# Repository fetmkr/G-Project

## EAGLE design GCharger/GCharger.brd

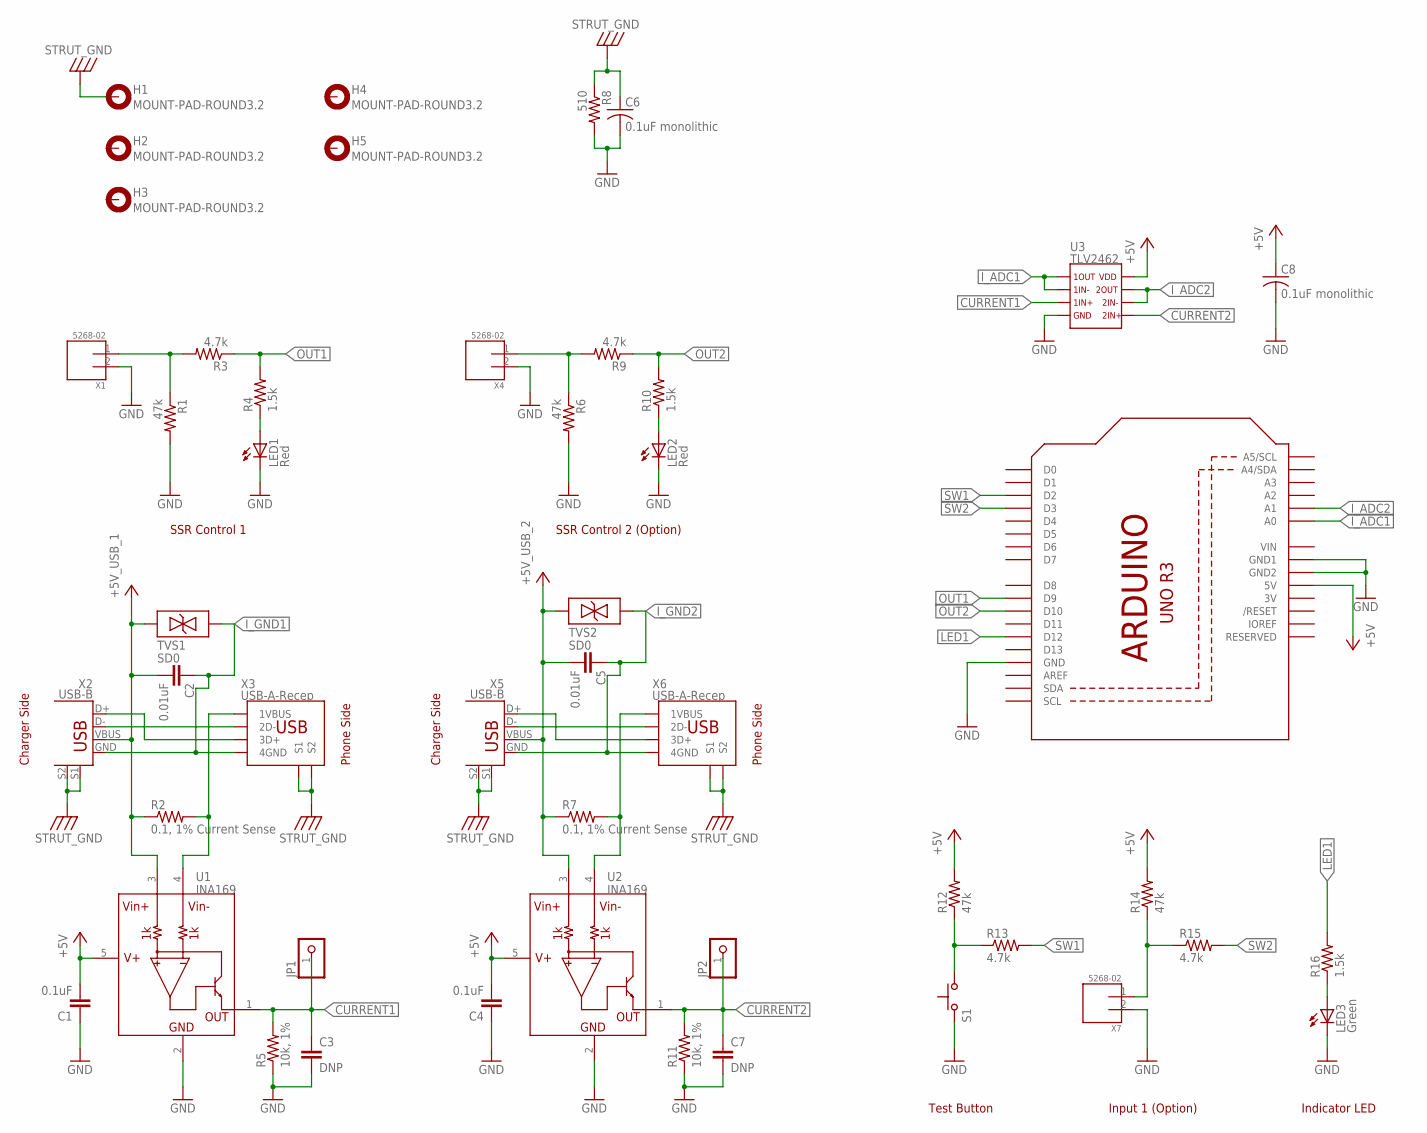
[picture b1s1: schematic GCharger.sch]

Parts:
C1, C4: 0.1uF; C0603(1608)
C2, C5: 0.01uF; C0603(1608)
C3, C7: DNP; C0603(1608)
C6, C8: 0.1uF monolithic; C050-024X044
H1, H2, H3, H4, H5: MOUNT-PAD-ROUND3.2; 3.2-PAD-ROUND
JP1, JP2: PINHD-1X1CB; 1X01-CLEANBIG
LED1, LED2: Red; LED3MM
LED3: Green; LED3MM
R1, R6, R12, R14: 47k; 0805-THM
R2, R7: 0.1, 1% Current Sense; 1206
R3, R9, R13, R15: 4.7k; 0805-THM
R4, R10, R16: 1.5k; 0805-THM
R5, R11: 10k, 1%; 0805-THM
R8: 510; 0805-THM
S1: SWITCH; SKHLACA010
TVS1, TVS2: SD0; SOD-323
U1, U2: INA169; SOT23-5
U3: TLV2462; SO8
U4: ARDUINOR3-TPLACE; ARDUINOR3
X1, X4, X7: 5268-02; 5628-02
X2, X5: USB-B; USB-B-PTH
X3, X6: USB-A-Recep; USB-A-RECEPT

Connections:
3V: U4.3V
+5V: C1.2, C4.2, C8.1, R12.2, R14.2, U1.5 (V+), U2.5 (V+), U3.8, U4.5V
+5V_USB_1: C2.2, R2.1, TVS1.1, U1.3 (VIN+), X2.VBUS
+5V_USB_2: C5.2, R7.1, TVS2.1, U2.3 (VIN+), X5.VBUS
CURRENT1: C3.1, JP1.1, R5.2, U1.1 (OUT), U3.3
CURRENT2: C7.1, JP2.1, R11.2, U2.1 (OUT), U3.5
GND: C1.1, C3.2, C4.1, C6.2, C7.2, C8.2, LED1.K (C), LED2.K (C), LED3.K (C), R1.2, R5.1, R6.2, R8.2, R11.1, S1.P$1, U1.2 (GND), U2.2 (GND), U3.4, U4.GND, U4.GND1, U4.GND2, X1.2, X4.2, X7.2
I_ADC1: U3.1, U3.2, U4.A0
I_ADC2: U3.6, U3.7, U4.A1
I_GND1: C2.1, TVS1.2, X2.GND, X3.4 (4GND)
I_GND2: C5.1, TVS2.2, X5.GND, X6.4 (4GND)
LED1: R16.2, U4.D12
unnamed: X5.D-, X6.2 (2D-)
unnamed: X5.D+, X6.3 (3D+)
unnamed: R1.1, R3.2, X1.1
unnamed: X2.D-, X3.2 (2D-)
unnamed: X2.D+, X3.3 (3D+)
unnamed: R7.2, U2.4 (VIN-), X6.1 (1VBUS)
unnamed: R12.1, R13.1, S1.P$2
unnamed: R6.1, R9.2, X4.1
unnamed: R2.2, U1.4 (VIN-), X3.1 (1VBUS)
unnamed: LED2.A, R10.1
unnamed: LED1.A, R4.1
unnamed: LED3.A, R16.1
unnamed: R14.1, R15.1, X7.1
OUT1: R3.1, R4.2, U4.D9
OUT2: R9.1, R10.2, U4.D10
STRUT_GND: C6.1, H1.B3,2, R8.1, X2.S1, X2.S2, X3.S1, X3.S2, X5.S1, X5.S2, X6.S1, X6.S2
SW1: R13.2, U4.D2
SW2: R15.2, U4.D3
VIN: U4.VIN

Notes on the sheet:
SSR Control 1
SSR Control 2 (Option)
Charger Side
Phone Side
Test Button
Input 1 (Option)
Indicator LED

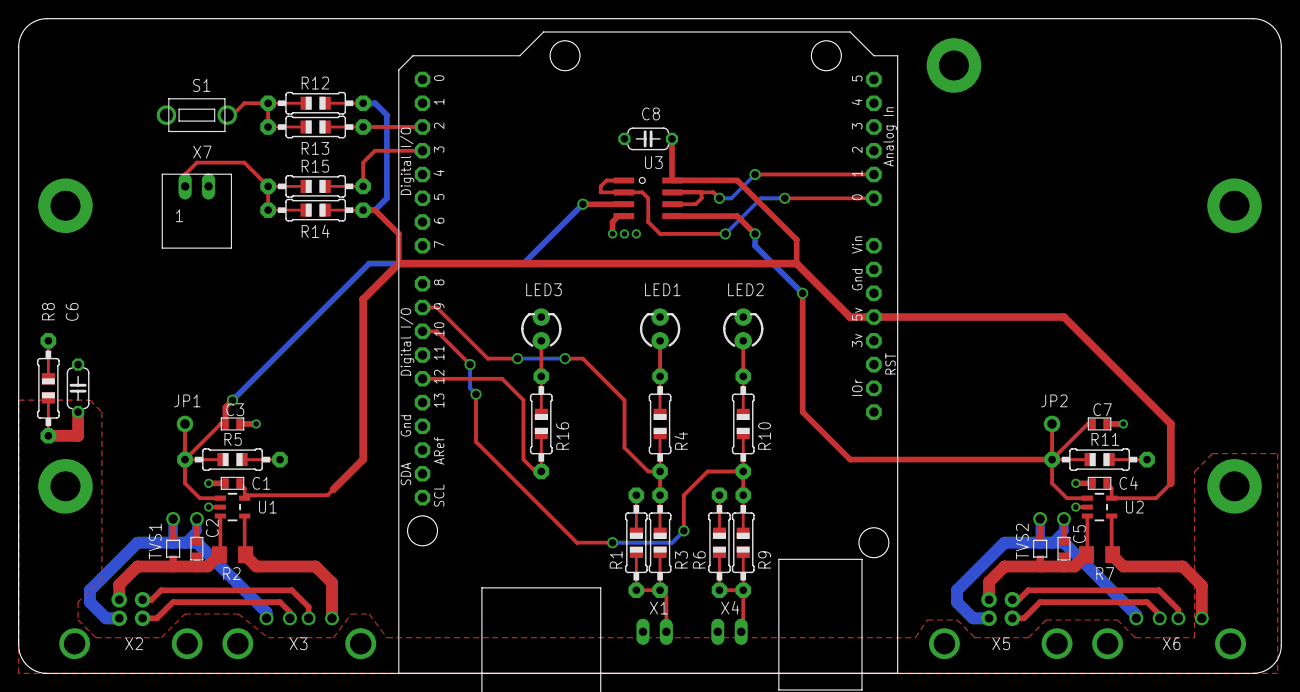
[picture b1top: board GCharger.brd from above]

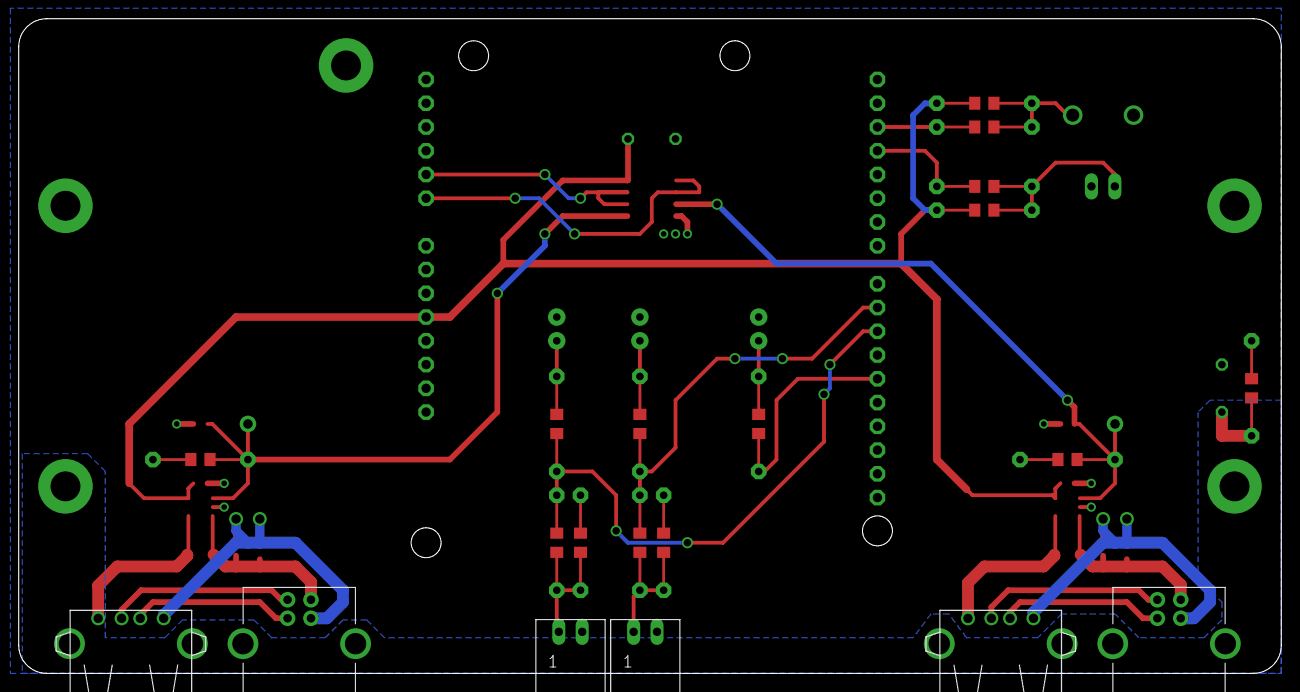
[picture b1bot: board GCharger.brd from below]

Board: 2 copper layers, 135.0 x 70.0 mm, 48 parts (6 on the bottom side), 29 nets.

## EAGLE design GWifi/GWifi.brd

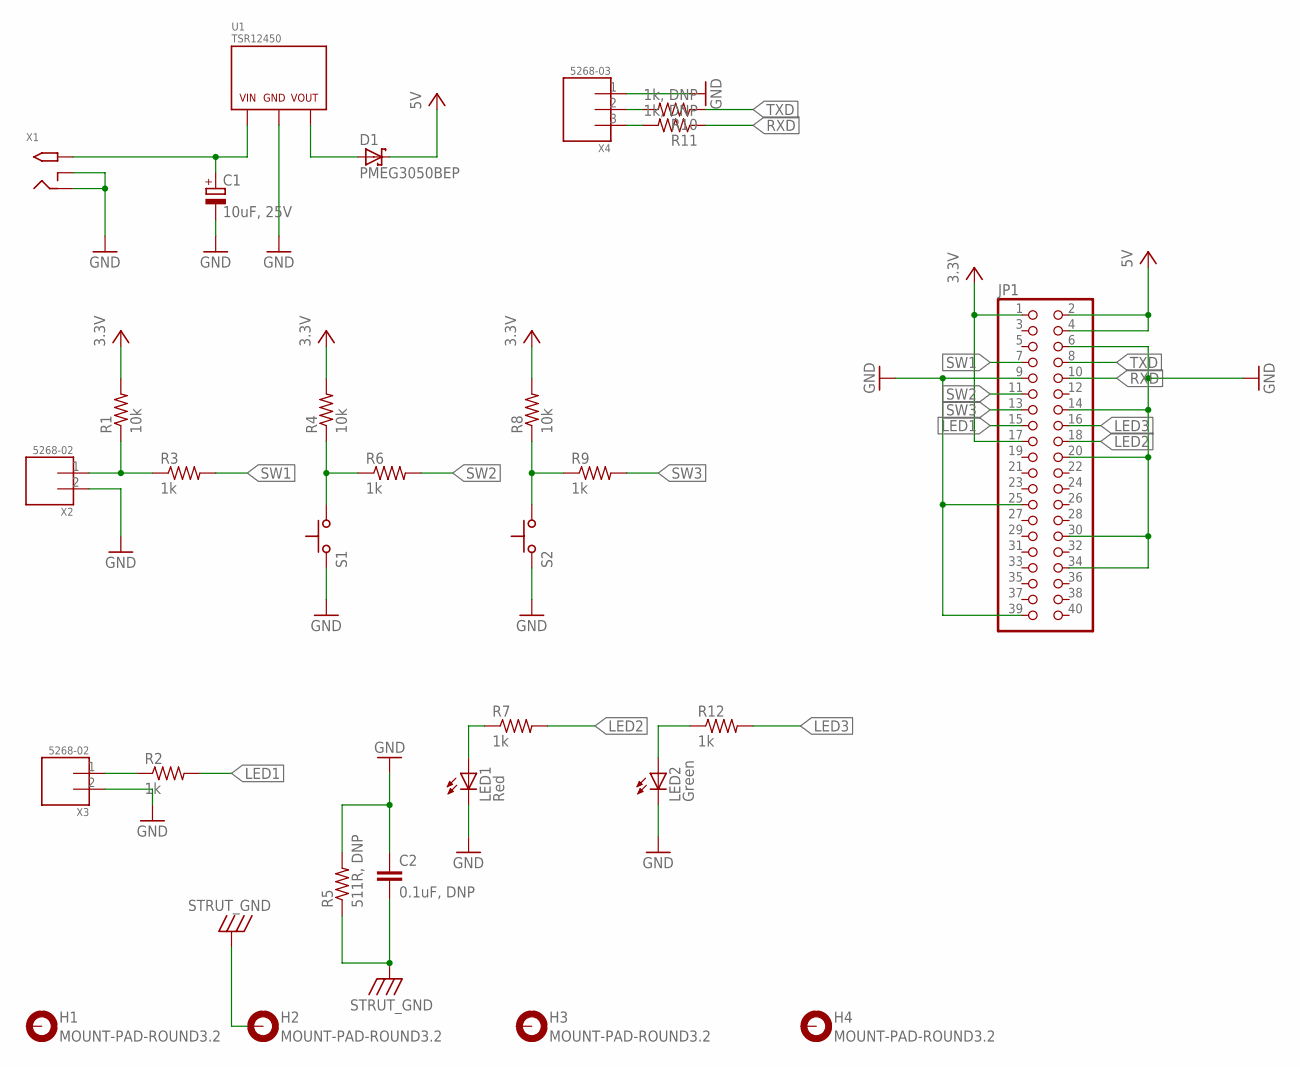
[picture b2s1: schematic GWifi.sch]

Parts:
C1: 10uF, 25V; C3528-TR3B
C2: 0.1uF, DNP; C0805(2012)
D1: PMEG3050BEP; PMEG6020EP
H1, H2, H3, H4: MOUNT-PAD-ROUND3.2; 3.2-PAD-ROUND
JP1: PINHD-2X20; 2X20
LED1: Red; LED3MM
LED2: Green; LED3MM
R1, R4, R8: 10k; 0805-THM
R2, R3, R6, R7, R9, R12: 1k; 0805-THM
R5: 511R, DNP; R0805(2012)
R10, R11: 1k, DNP; R0805(2012)
S1, S2: SWITCH; SKHLACA010
U1: TSR12450
X1: 2.1MMJACKTHM; PJ-102A
X2, X3: 5268-02; 5628-02
X4: 5268-03

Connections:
3.3V: JP1.1, JP1.17, R1.2, R4.2, R8.2
5V: D1.C, JP1.2, JP1.4
GND: C1.-, C2.1, JP1.6, JP1.9, JP1.14, JP1.20, JP1.25, JP1.30, JP1.34, JP1.39, LED1.K (C), LED2.K (C), R5.2, S1.P$1, S2.P$1, U1.GND (2), X1.RING, X1.RING_SW, X2.2, X3.2, X4.1
LED1: JP1.15, R2.2
LED2: JP1.18, R7.2
LED3: JP1.16, R12.2
unnamed: C1.+, U1.VIN (1), X1.TIP
unnamed: D1.A, U1.VOUT (3)
unnamed: R1.1, R3.1, X2.1
unnamed: R10.2, X4.2
unnamed: R11.2, X4.3
unnamed: R4.1, R6.1, S1.P$2
unnamed: R8.1, R9.1, S2.P$2
unnamed: R2.1, X3.1
unnamed: LED1.A, R7.1
unnamed: LED2.A, R12.1
RXD: JP1.10, R11.1
STRUT_GND: C2.2, H2.B3,2, R5.1
SW1: JP1.7, R3.2
SW2: JP1.11, R6.2
SW3: JP1.13, R9.2
TXD: JP1.8, R10.1

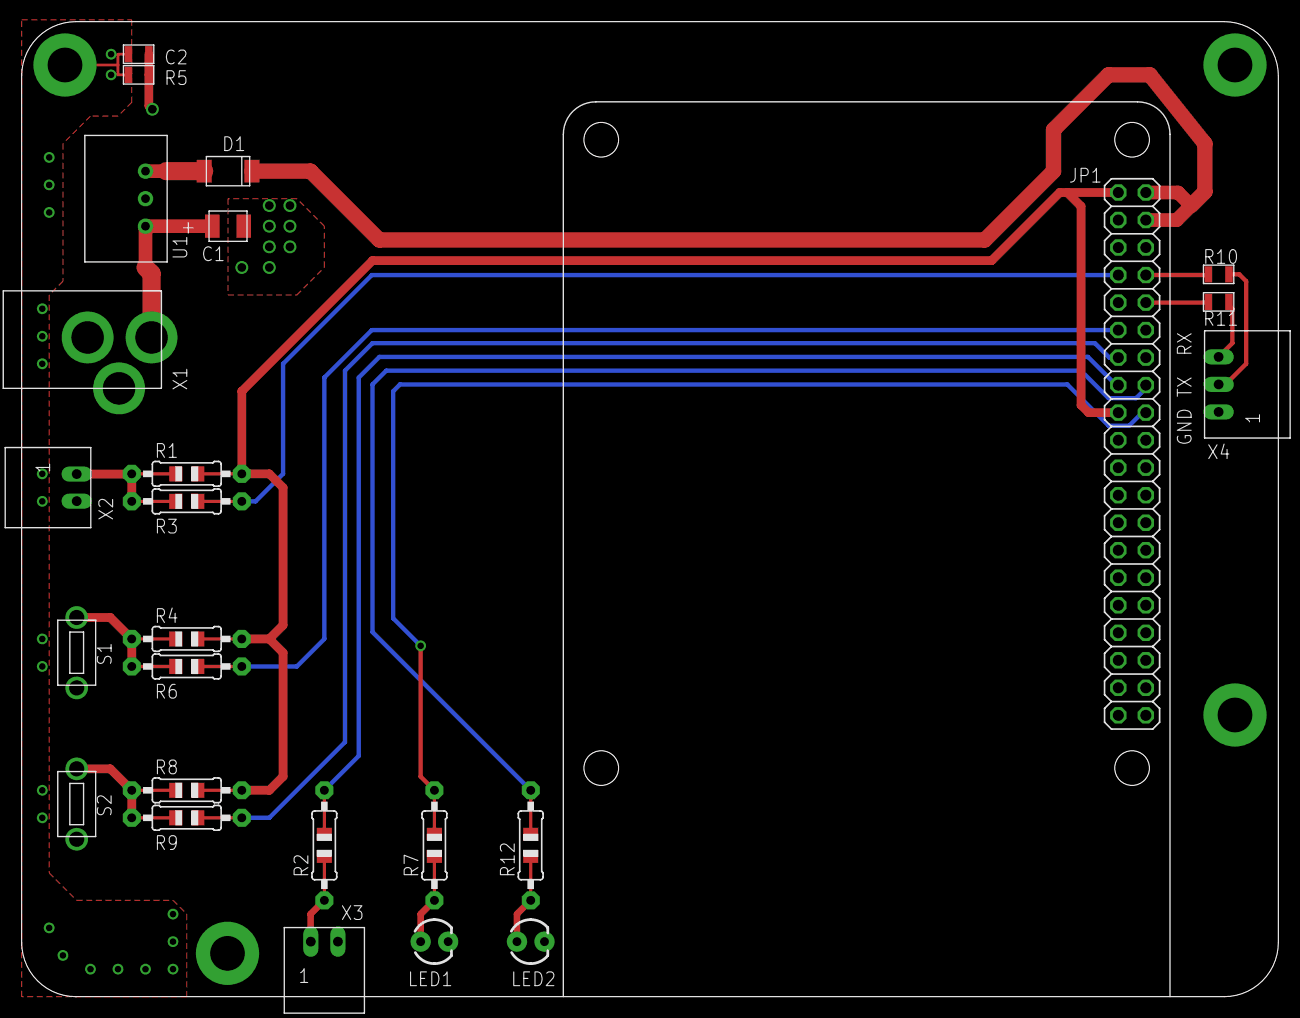
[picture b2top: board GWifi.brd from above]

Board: 2 copper layers, 116.0 x 90.0 mm, 29 parts (0 on the bottom side), 22 nets.

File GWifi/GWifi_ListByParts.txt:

Part	Value	Attributes	Package	Description	Part Num
C1	10uF, 25V		C3528-TR3B		*
C2	0.1uF, DNP		C0805(2012)		*
D1	PMEG3050BEP		PMEG6020EP		*
H1	MOUNT-PAD-ROUND3.2		3.2-PAD-ROUND		*
H2	MOUNT-PAD-ROUND3.2		3.2-PAD-ROUND		*
H3	MOUNT-PAD-ROUND3.2		3.2-PAD-ROUND		*
H4	MOUNT-PAD-ROUND3.2		3.2-PAD-ROUND		*
JP1			2X20	PIN HEADER	*
LED1	Red		LED3MM	LEDs	*
LED2	Green		LED3MM	LEDs	*
R1	10k		0805-THM	RESISTOR, American symbol	*
R2	1k		0805-THM	RESISTOR, American symbol	*
R3	1k		0805-THM	RESISTOR, American symbol	*
R4	10k		0805-THM	RESISTOR, American symbol	*
R5	511R, DNP		R0805(2012)		*
R6	1k		0805-THM	RESISTOR, American symbol	*
R7	1k		0805-THM	RESISTOR, American symbol	*
R8	10k		0805-THM	RESISTOR, American symbol	*
R9	1k		0805-THM	RESISTOR, American symbol	*
R10	1k, DNP		R0805(2012)		*
R11	1k, DNP		R0805(2012)		*
R12	1k		0805-THM	RESISTOR, American symbol	*
S1			SKHLACA010		*
S2			SKHLACA010		*
U1	TSR12450		TSR12450		*
X1	2.1MMJACKTHM		PJ-102A	2.1mm x 5.5mm THM DC jack with internal switch. Digikey part #PJ-102A, 4UCON part #05537	*
X2	5268-02		5628-02		*
X3	5268-02		5628-02		*
X4	5268-03		5268-03		*

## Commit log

2015-02-05 :neckbeard: Added .gitattributes & .gitignore files
2015-02-05 first
2015-02-05 pdf deleted
2015-02-05 Gcharger Project Created
2015-02-05 pl added
2015-02-06 gpio description, sch pdf added
2015-02-15 Gcharger Board
2015-02-16 gerber file added
2015-02-16 value corrected

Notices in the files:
parts and their libraries:
SparkFun-LED: Licensing: CC v3.0 Share-Alike You are welcome to use this library for commercial purposes.
SparkFun-Resistors: Licensing: Creative Commons ShareAlike 4.0 International - https://creativecommons.org/licenses/by-sa/4.0
